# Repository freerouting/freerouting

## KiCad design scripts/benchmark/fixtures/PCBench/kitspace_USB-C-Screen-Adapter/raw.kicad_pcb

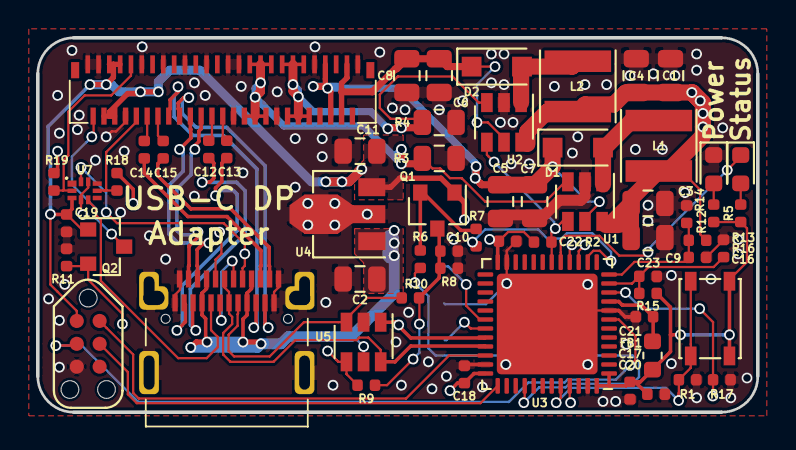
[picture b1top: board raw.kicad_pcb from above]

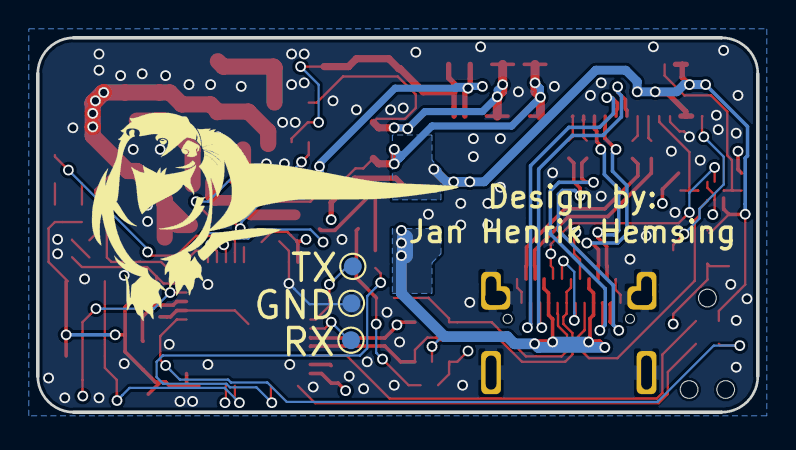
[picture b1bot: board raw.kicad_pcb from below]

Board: 4 copper layers, 40.0 x 20.8 mm, 64 parts (3 on the bottom side), 51 nets.

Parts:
C1, C2, C3, C4, C5, C6, C7, C8, C9, C11: 2.2uF; C_0805_2012Metric
C10: 820p; C_0402_1005Metric
C12, C13, C14, C15, C16, C17, C18, C19, C20, C21, C22: 100n; C_0402_1005Metric
C23: 220n; C_0402_1005Metric
D1, D2: SM4007PL; D_SOD-123F
D3, D4: LED; LED_0603_1608Metric
FB1: FERRET; L_0603_1608Metric
J1: USB_C_Receptacle; USB_C_24P_SMD
L1, L2: 22uH; L_Taiyo-Yuden_MD-4040
P1: TC2030-CTX-Tag-Connect; TC2030
Q1, Q2: 2N7002; SOT-23
R1, R2, R8: 5k1; R_0402_1005Metric
R3, R4: 0.8; R_0805_2012Metric
R5, R12: 1k; R_0402_1005Metric
R6: 169; R_0402_1005Metric
R7: 75; R_0402_1005Metric
R9, R10, R18, R19: 0; R_0402_1005Metric
R11: 1M; R_0402_1005Metric
R13: 8k2; R_0402_1005Metric
R14: 1k5; R_0402_1005Metric
R15, R17: 24k; R_0402_1005Metric
R16: 4k7; R_0402_1005Metric
SW1: DFU; SW_SPST_PTS810
TP1: UART_TX; TestPoint_Pad_D1.0mm
TP2: UART_RX; TestPoint_Pad_D1.0mm
TP3: GND; TestPoint_Pad_D1.0mm
U1, U2: SY7200AABC; SOT-23-6
U3: STM32F072CBUx; QFN-48-1EP_7x7mm_P0.5mm_EP5.6x5.6mm
U4: AP2204R-3.3; SOT-89-3
U5: USBLC6-4; SOT-23-6
U6: 5022505191
U7: STG3684A; QFN10L

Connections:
+3V3: C11.1, C17.1, C18.1, C19.1, C20.1, C22.1, FB1.2, P1.1, Q1.1, Q2.1, R2.1, R5.2, R12.2, R15.2, SW1.2, U3.1, U3.24, U3.36, U3.48, U4.3, U6.4, U6.5, U6.6, U6.7, U7.3
+5V: C1.1, C2.1, C3.1, C4.1, C9.1, J1.A4, J1.A9, J1.B4, J1.B9, L1.1, L2.1, R13.2, U1.6, U2.6, U4.1, U5.5
/_L0_N: C14.2, J1.A10
/_L0_P: C15.2, J1.A11
/_L3_N: C12.2, J1.B10
/_L3_P: C13.2, J1.B11
AUX_N: R18.1, U6.10, U7.7
AUX_P: R19.1, U6.9, U7.2
CC1: J1.A5, R9.1, U5.4
CC2: J1.B5, R10.1, U5.3
CC_RX: R7.2, U3.14
CC_TX: R6.2, U3.40
DFU: R1.2, SW1.1, U3.44
GND: C1.2, C2.2, C3.2, C4.2, C5.2, C6.2, C7.2, C8.2, C9.2, C10.2, C11.2, C16.2, C17.2, C18.2, C19.2, C20.2, C21.2, C22.2, C23.2, D4.1, J1.A1, J1.A12, J1.B1, J1.B12, J1.S1, P1.5, R1.1, R3.2, R4.2, R8.2, R11.1, R14.1, R16.1, R17.1, TP3.1, U1.2, U2.2, U3.8, U3.23, U3.35, U3.47, U3.49, U4.2, U5.2, U6.1, U6.3, U6.8, U6.11, U6.15, U6.19, U6.23, U6.27, U6.28, U6.29, U6.36, U6.43, U6.51, U7.8
HPD: Q2.3, U6.2
L0_N: C14.1, U6.12
L0_P: C15.1, U6.14
L1_N: J1.B3, U6.16
L1_P: J1.B2, U6.18
L2_N: J1.A3, U6.20
L2_P: J1.A2, U6.22
L3_N: C12.1, U6.24
L3_P: C13.1, U6.26
LEDA1: C6.1, C8.1, D2.1, U2.5, U6.48, U6.49
LEDA2: C5.1, C7.1, D1.1, U1.5, U6.45, U6.46
LEDC1: R4.1, U2.3, U6.37, U6.38, U6.39, U6.40, U6.41, U6.42
LEDC2: R3.1, U1.3, U6.30, U6.31, U6.32, U6.33, U6.34, U6.35
NRST: P1.3, U3.7
unnamed: C10.1, Q1.3, R8.1, R9.2, R10.2
unnamed: D1.2, L1.2, U1.1
unnamed: D2.2, L2.2, U2.1
unnamed: D3.1, U3.17
unnamed: D3.2, R5.1
unnamed: D4.2, R12.1
unnamed: Q1.2, R6.1, R7.1
unnamed: TP1.1, U3.30
unnamed: TP2.1, U3.31
PWM: R2.2, U1.4, U2.4, U3.18
RXREF: C23.1, R15.1, R16.2, U3.11
SBU1: J1.A8, U7.10
SBU2: J1.B8, U7.5
SBU_ENABLE: R17.2, U3.10, U7.4, U7.9
STM_HPD: Q2.2, R11.2, U3.45
SWCLK: P1.4, U3.37
SWDIO: P1.2, U3.34
USB_N: J1.A7, J1.B7, U3.32, U5.1
USB_P: J1.A6, J1.B6, U3.33, U5.6
VBUS_SENSE: C16.1, R13.1, R14.2, U3.12
VDDA: C21.1, FB1.1, U3.9
_DP_AUX_N: R18.2, U3.15
_DP_AUX_P: R19.2, U3.16

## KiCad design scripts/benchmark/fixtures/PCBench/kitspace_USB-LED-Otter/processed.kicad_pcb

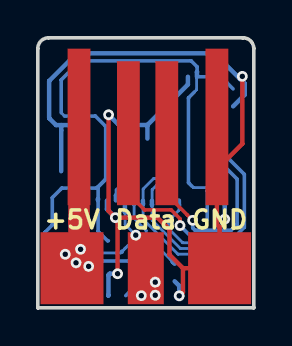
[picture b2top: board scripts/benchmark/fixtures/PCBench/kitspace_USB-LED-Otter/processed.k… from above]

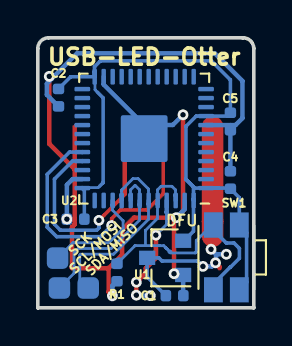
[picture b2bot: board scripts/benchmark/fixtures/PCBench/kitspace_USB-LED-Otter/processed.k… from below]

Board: 2 copper layers, 12.0 x 15.0 mm, 14 parts (12 on the bottom side), 10 nets.

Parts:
C1, C2, C3, C4, C5: 100n; C_0402_1005Metric
J1: USB; USBPCB
J2, J4, J5: PAD; Pad_0.80.8
J3: LED; LED-Strip
R1: 10k; R_0402_1005Metric
SW1: DFU; SW_SPST_EVQP7A
U1: MCP1700-3302E_SOT23; SOT-23
U2: STM32F072CBUx; QFN-48-1EP_7x7mm_P0.5mm_EP2.6x2.6mm

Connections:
+3V3: C2.1, C3.1, C4.1, C5.1, SW1.2, U1.2, U2.1, U2.9, U2.24, U2.36, U2.48
+5V: C1.1, J1.1, J3.1, U1.3
GND: C1.2, C2.2, C3.2, C4.2, C5.2, J1.4, J3.3, R1.2, U1.1, U2.8, U2.23, U2.35, U2.47, U2.49
LED: J3.2, U2.45
unnamed: R1.1, SW1.1, U2.44, U2.46
SCK: J5.1, U2.39
SCL: J2.1, U2.41, U2.42
SDA: J4.1, U2.40, U2.43
USB_N: J1.2, U2.32
USB_P: J1.3, U2.33

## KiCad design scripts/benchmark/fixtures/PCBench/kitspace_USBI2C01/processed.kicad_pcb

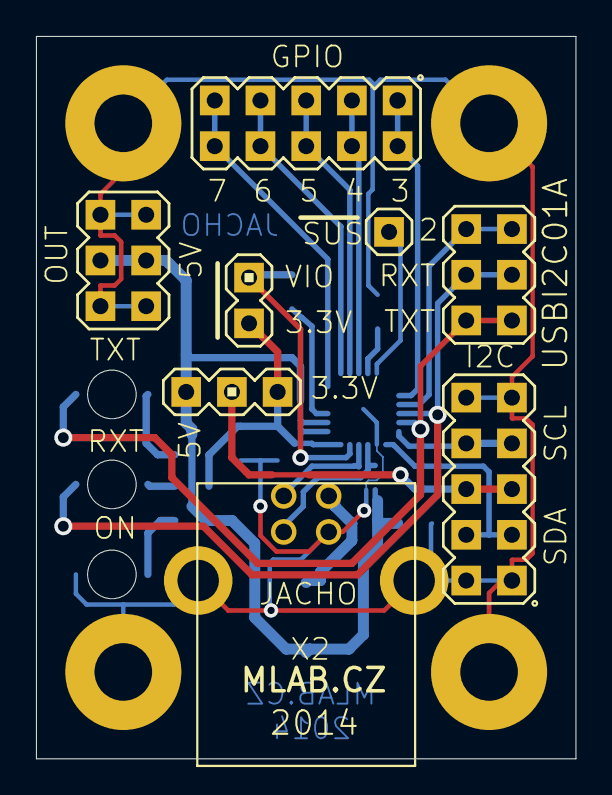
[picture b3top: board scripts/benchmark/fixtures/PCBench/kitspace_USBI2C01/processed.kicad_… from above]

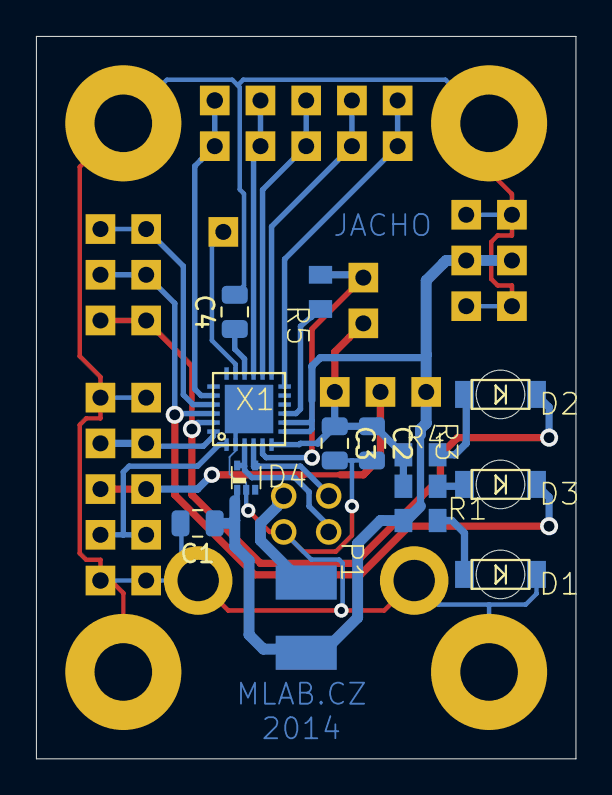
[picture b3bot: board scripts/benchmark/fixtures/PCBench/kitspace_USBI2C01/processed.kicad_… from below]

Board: 2 copper layers, 30.0 x 40.1 mm, 26 parts (14 on the bottom side), 24 nets.

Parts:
C1: 1uF; C_0805_2012Metric
C2: 10uF; C_0805_2012Metric
C3: 100nF; C_0805_2012Metric
C4: 4u7; C_0805_2012Metric
D1: ZELENA; 1206_2
D2, D3: CERVENA; 1206_2
D4: SP1001-04XTG; SOT553
P1: 750mA; 1812
R1, R3, R4: 470R; 0805
R5: 4k7; 0805
SV1: MA02-1
SV2, SV5: MA05-2
SV3: MA03-1
SV4, SV6: MA03-2
SV7: MA01-1
X1: CP2112; QFN-24
X2: USB_B
X3, X4, X5, X6: SROUB3M

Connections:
+3.3V: C2.1, C3.1, R3.1, R4.1, SV1.1, SV3.1, X1.P$6
+5V: C1.1, D4.1, P1.2, R1.2, SV3.3, SV6.3, SV6.4, X1.P$7, X1.P$8
GND: C1.2, C2.2, C3.2, C4.2, D1.K, D4.2, SV2.1, SV2.2, SV2.9, SV2.10, SV6.1, SV6.2, SV6.5, SV6.6, X1.P$2, X1.P$25, X2.4, X2.GND, X2.GND2, X3.P$1, X4.P$1, X5.P$1, X6.P$1
unnamed: C4.1, X1.P$16
unnamed: D1.A, R1.1
unnamed: D2.A, R4.2
unnamed: D2.K, SV4.1, SV4.2, X1.P$23
unnamed: D3.A, R3.2
unnamed: D4.4, X1.P$4, X2.2
unnamed: D4.5, X1.P$3, X2.3
unnamed: P1.1, X2.1
unnamed: R5.1, X1.P$9
unnamed: R5.2, SV1.2, X1.P$5
unnamed: SV2.5, SV2.6, SV3.2
unnamed: SV5.1, SV5.2, X1.P$20
unnamed: SV7.1, X1.P$17
unnamed: SV2.3, SV2.4, X1.P$1
unnamed: SV5.9, SV5.10, X1.P$12
unnamed: SV5.7, SV5.8, X1.P$13
unnamed: SV5.5, SV5.6, X1.P$14
unnamed: SV5.3, SV5.4, X1.P$15
unnamed: SV4.5, SV4.6, X1.P$21
unnamed: D3.K, SV4.3, SV4.4, X1.P$22
unnamed: SV2.7, SV2.8, X1.P$24
